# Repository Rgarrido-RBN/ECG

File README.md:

# ECG
Simplified PCB of analog ECG used for educational purposes

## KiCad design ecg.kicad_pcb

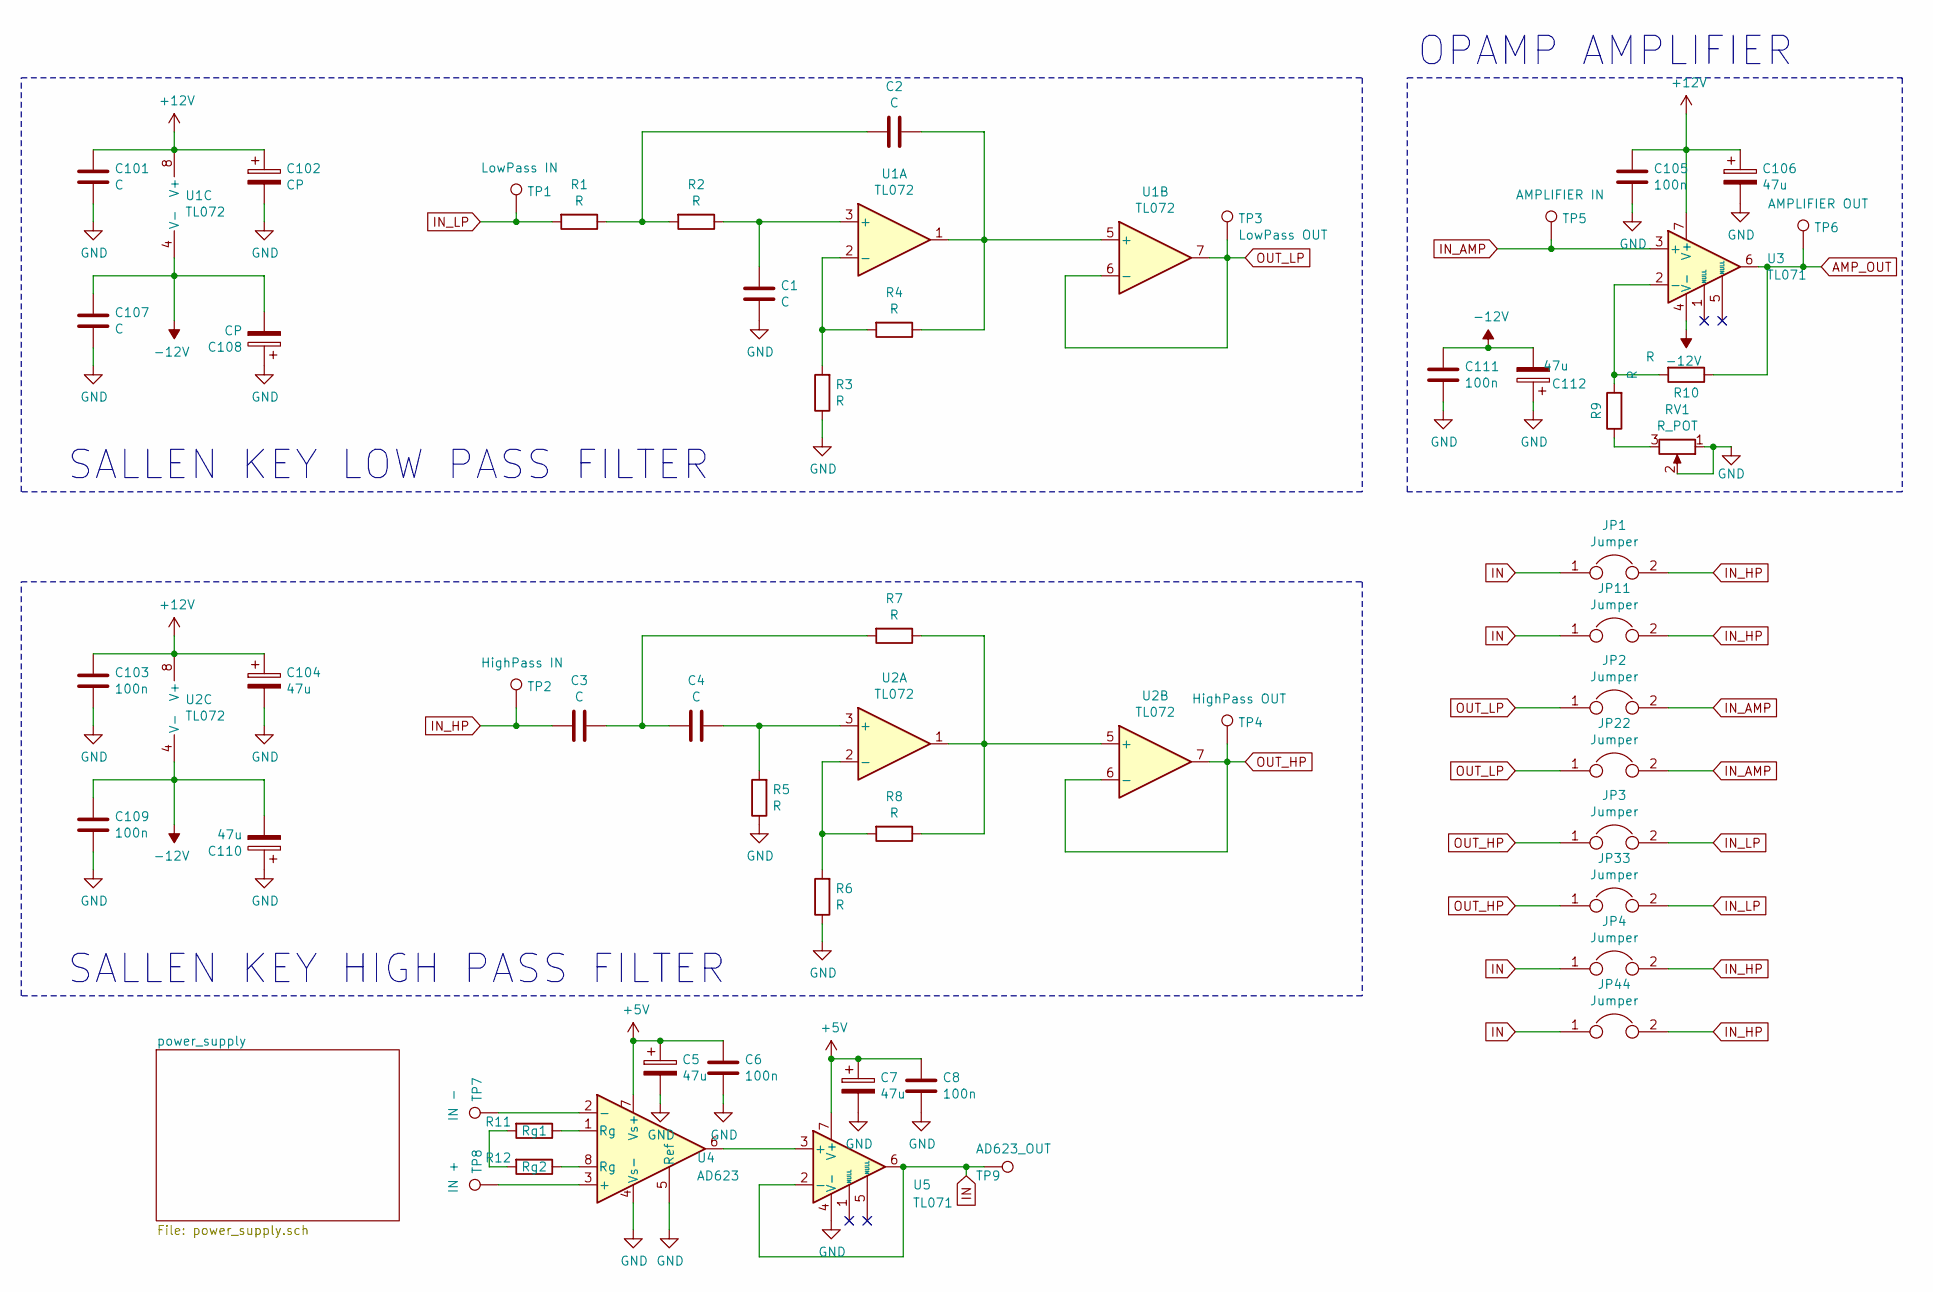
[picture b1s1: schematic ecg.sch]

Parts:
C1, C2, C3, C4, C101, C107: C; C_Rect_L7.2mm_W4.5mm_P5.00mm_FKS2_FKP2_MKS2_MKP2
C5, C7, C104, C106, C110, C112: 47u; CP_Radial_D7.5mm_P2.50mm
C6, C8, C103, C105, C109, C111: 100n; C_Rect_L7.2mm_W4.5mm_P5.00mm_FKS2_FKP2_MKS2_MKP2
C102, C108: CP; CP_Radial_D7.5mm_P2.50mm
JP1, JP2, JP3, JP4, JP11, JP22, JP33, JP44: Jumper; PinHeader_1x02_P1.27mm_Vertical
R1, R2, R3, R4, R5, R6, R7, R8, R9, R10: R; R_Axial_DIN0207_L6.3mm_D2.5mm_P10.16mm_Horizontal
R11: Rg1; R_Axial_DIN0207_L6.3mm_D2.5mm_P10.16mm_Horizontal
R12: Rg2; R_Axial_DIN0207_L6.3mm_D2.5mm_P10.16mm_Horizontal
RV1: R_POT; Potentiometer_Piher_PT-6-V_Vertical
TP1: LowPass IN; PinHeader_1x01_P1.27mm_Vertical
TP2: HighPass IN; PinHeader_1x01_P1.27mm_Vertical
TP3: LowPass OUT; PinHeader_1x01_P1.27mm_Vertical
TP4: HighPass OUT; PinHeader_1x01_P1.27mm_Vertical
TP5: AMPLIFIER IN; PinHeader_1x01_P1.27mm_Vertical
TP6: AMPLIFIER OUT; PinHeader_1x01_P1.27mm_Vertical
TP7: IN -; PinHeader_1x01_P1.27mm_Vertical
TP8: IN +; PinHeader_1x01_P1.27mm_Vertical
TP9: AD623_OUT; PinHeader_1x01_P1.27mm_Vertical
U1, U2: TL072; DIP-8_W7.62mm_LongPads
U3, U5: TL071; DIP-8_W7.62mm_LongPads
U4: AD623; DIP-8_W7.62mm_LongPads

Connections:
+5V: C5.1, C6.1, C7.1, C8.1, U4.7 (Vs+), U5.7 (V+); also elsewhere on the board
+12V: C101.1, C102.1, C103.1, C104.1, C105.1, C106.1, U1.8 (V+), U2.8 (V+), U3.7 (V+); also elsewhere on the board
-12V: C107.1, C108.2, C109.1, C110.2, C111.1, C112.2, U1.4 (V-), U2.4 (V-), U3.4 (V-); also elsewhere on the board
AMP_OUT: R10.1, TP6.1, U3.6
GND: C1.2, C5.2, C6.2, C7.2, C8.2, C101.2, C102.2, C103.2, C104.2, C105.2, C106.2, C107.2, C108.1, C109.2, C110.1, C111.2, C112.1, R3.1, R5.1, R6.1, RV1.1, RV1.2, U4.4 (Vs-), U4.5 (Ref), U5.4 (V-); also elsewhere on the board
IN: JP1.1, JP4.1, JP11.1, JP44.1, TP9.1, U5.2 (-), U5.6
IN_AMP: JP2.2, JP22.2, TP5.1, U3.3 (+)
IN_HP: C3.2, JP1.2, JP4.2, JP11.2, JP44.2, TP2.1
IN_LP: JP3.2, JP33.2, R1.2, TP1.1
unnamed: C1.1, R2.1, U1.3 (+)
unnamed: C2.1, R1.1, R2.2
unnamed: C2.2, R4.1, U1.1, U1.5 (+)
unnamed: C3.1, C4.1, R7.2
unnamed: C4.2, R5.2, U2.3 (+)
unnamed: R3.2, R4.2, U1.2 (-)
unnamed: R6.2, R8.2, U2.2 (-)
unnamed: R7.1, R8.1, U2.1, U2.5 (+)
unnamed: R9.1, RV1.3
unnamed: R9.2, R10.2, U3.2 (-)
unnamed: R11.1, U4.1 (Rg)
unnamed: R11.2, R12.2
unnamed: R12.1, U4.8 (Rg)
unnamed: TP7.1, U4.2 (-)
unnamed: TP8.1, U4.3 (+)
unnamed: U4.6, U5.3 (+)
OUT_HP: JP3.1, JP33.1, TP4.1, U2.6 (-), U2.7
OUT_LP: JP2.1, JP22.1, TP3.1, U1.6 (-), U1.7

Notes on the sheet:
SALLEN KEY LOW PASS FILTER
SALLEN KEY HIGH PASS FILTER
OPAMP AMPLIFIER

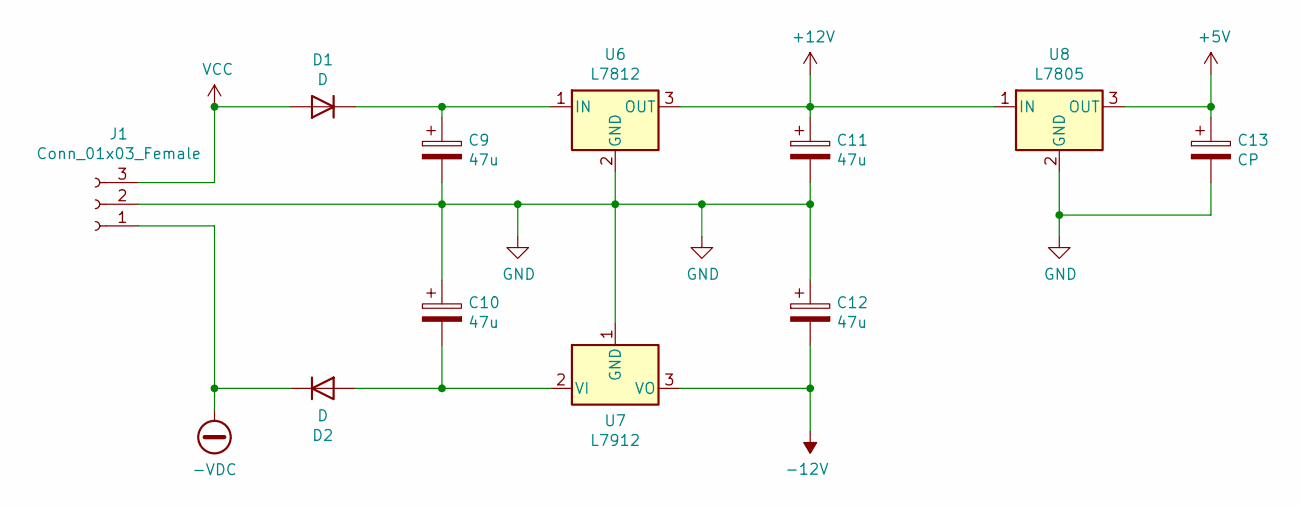
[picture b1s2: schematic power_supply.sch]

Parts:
C9, C10, C11, C12: 47u; CP_Radial_D7.5mm_P2.50mm
C13: CP; CP_Radial_D7.5mm_P2.50mm
D1, D2: D; D_DO-15_P15.24mm_Horizontal
J1: Conn_01x03_Female; PinHeader_1x03_P2.54mm_Vertical
U6: L7812; TO-220-3_Vertical
U7: L7912; TO-220-3_Vertical
U8: L7805; TO-220-3_Vertical

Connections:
+5V: C13.1, U8.3 (OUT); also elsewhere on the board
+12V: C11.1, U6.3 (OUT), U8.1 (IN); also elsewhere on the board
-12V: C12.2, U7.3 (VO); also elsewhere on the board
-VDC: D2.1 (K), J1.1
GND: C9.2, C10.1, C11.2, C12.1, C13.2, J1.2, U6.2 (GND), U7.1 (GND), U8.2 (GND); also elsewhere on the board
unnamed: C9.1, D1.1 (K), U6.1 (IN)
unnamed: C10.2, D2.2 (A), U7.2 (VI)
VCC: D1.2 (A), J1.3

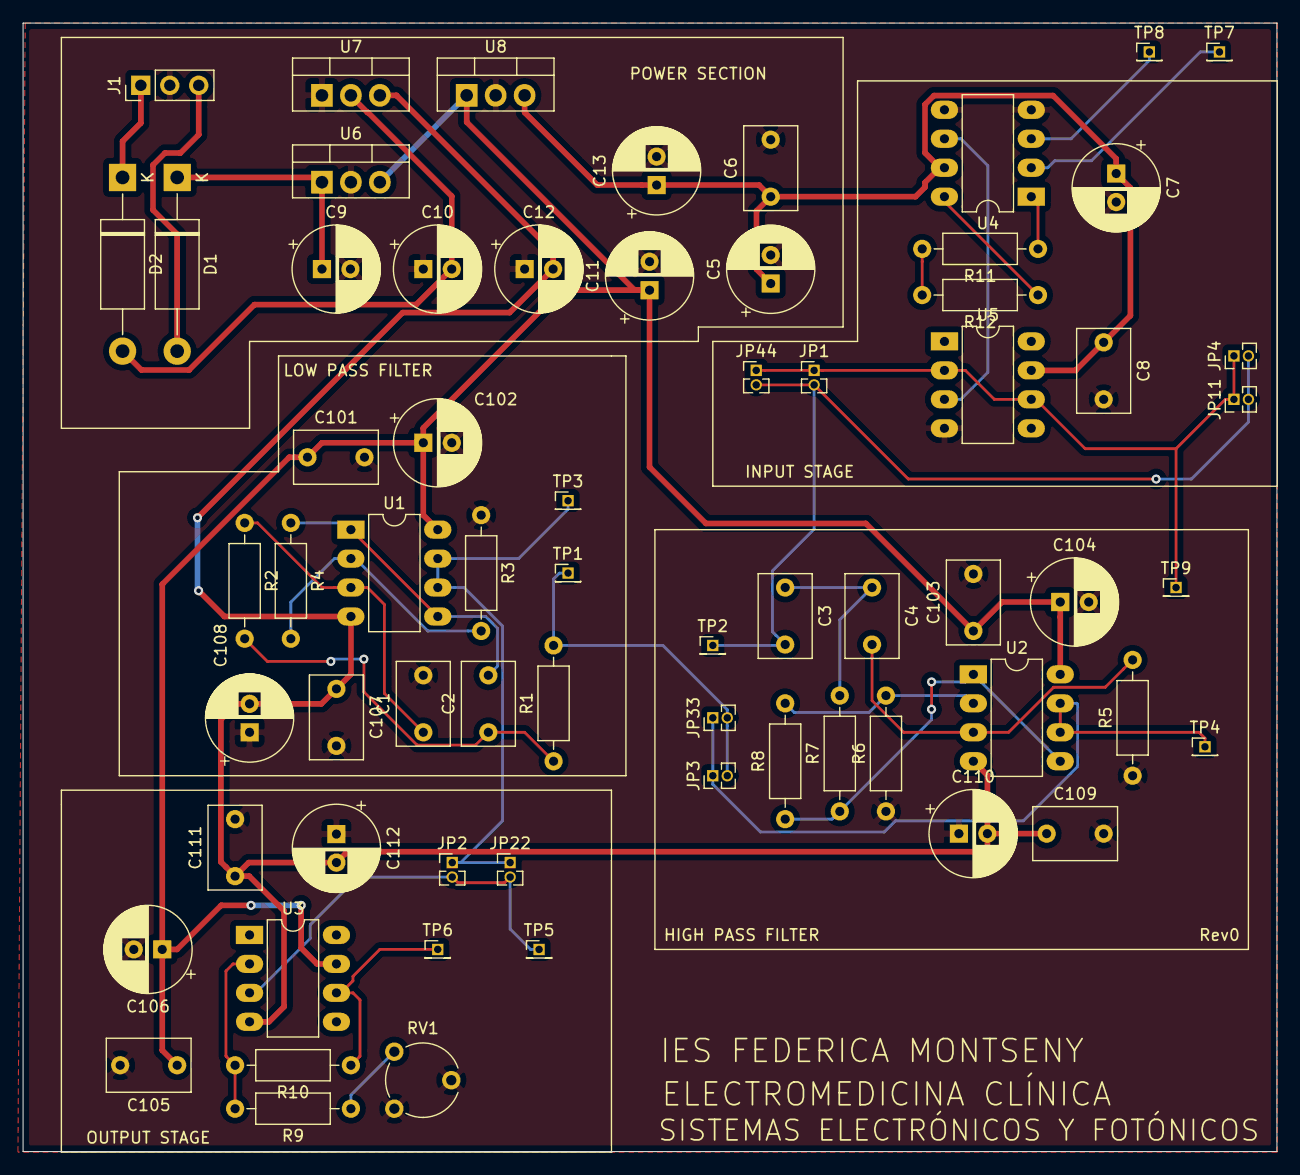
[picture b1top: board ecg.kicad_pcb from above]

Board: 2 copper layers, 110.0 x 99.0 mm, 66 parts (0 on the bottom side), 31 nets.

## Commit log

2021-09-20 fisrt commit
2021-09-20 Sallen Key cells and opamp added
2021-09-20 removing unnecesari files
2021-11-17 work in progress pcb layout
2021-11-18 pcb layout routed
2021-11-18 layout and fSilk added
